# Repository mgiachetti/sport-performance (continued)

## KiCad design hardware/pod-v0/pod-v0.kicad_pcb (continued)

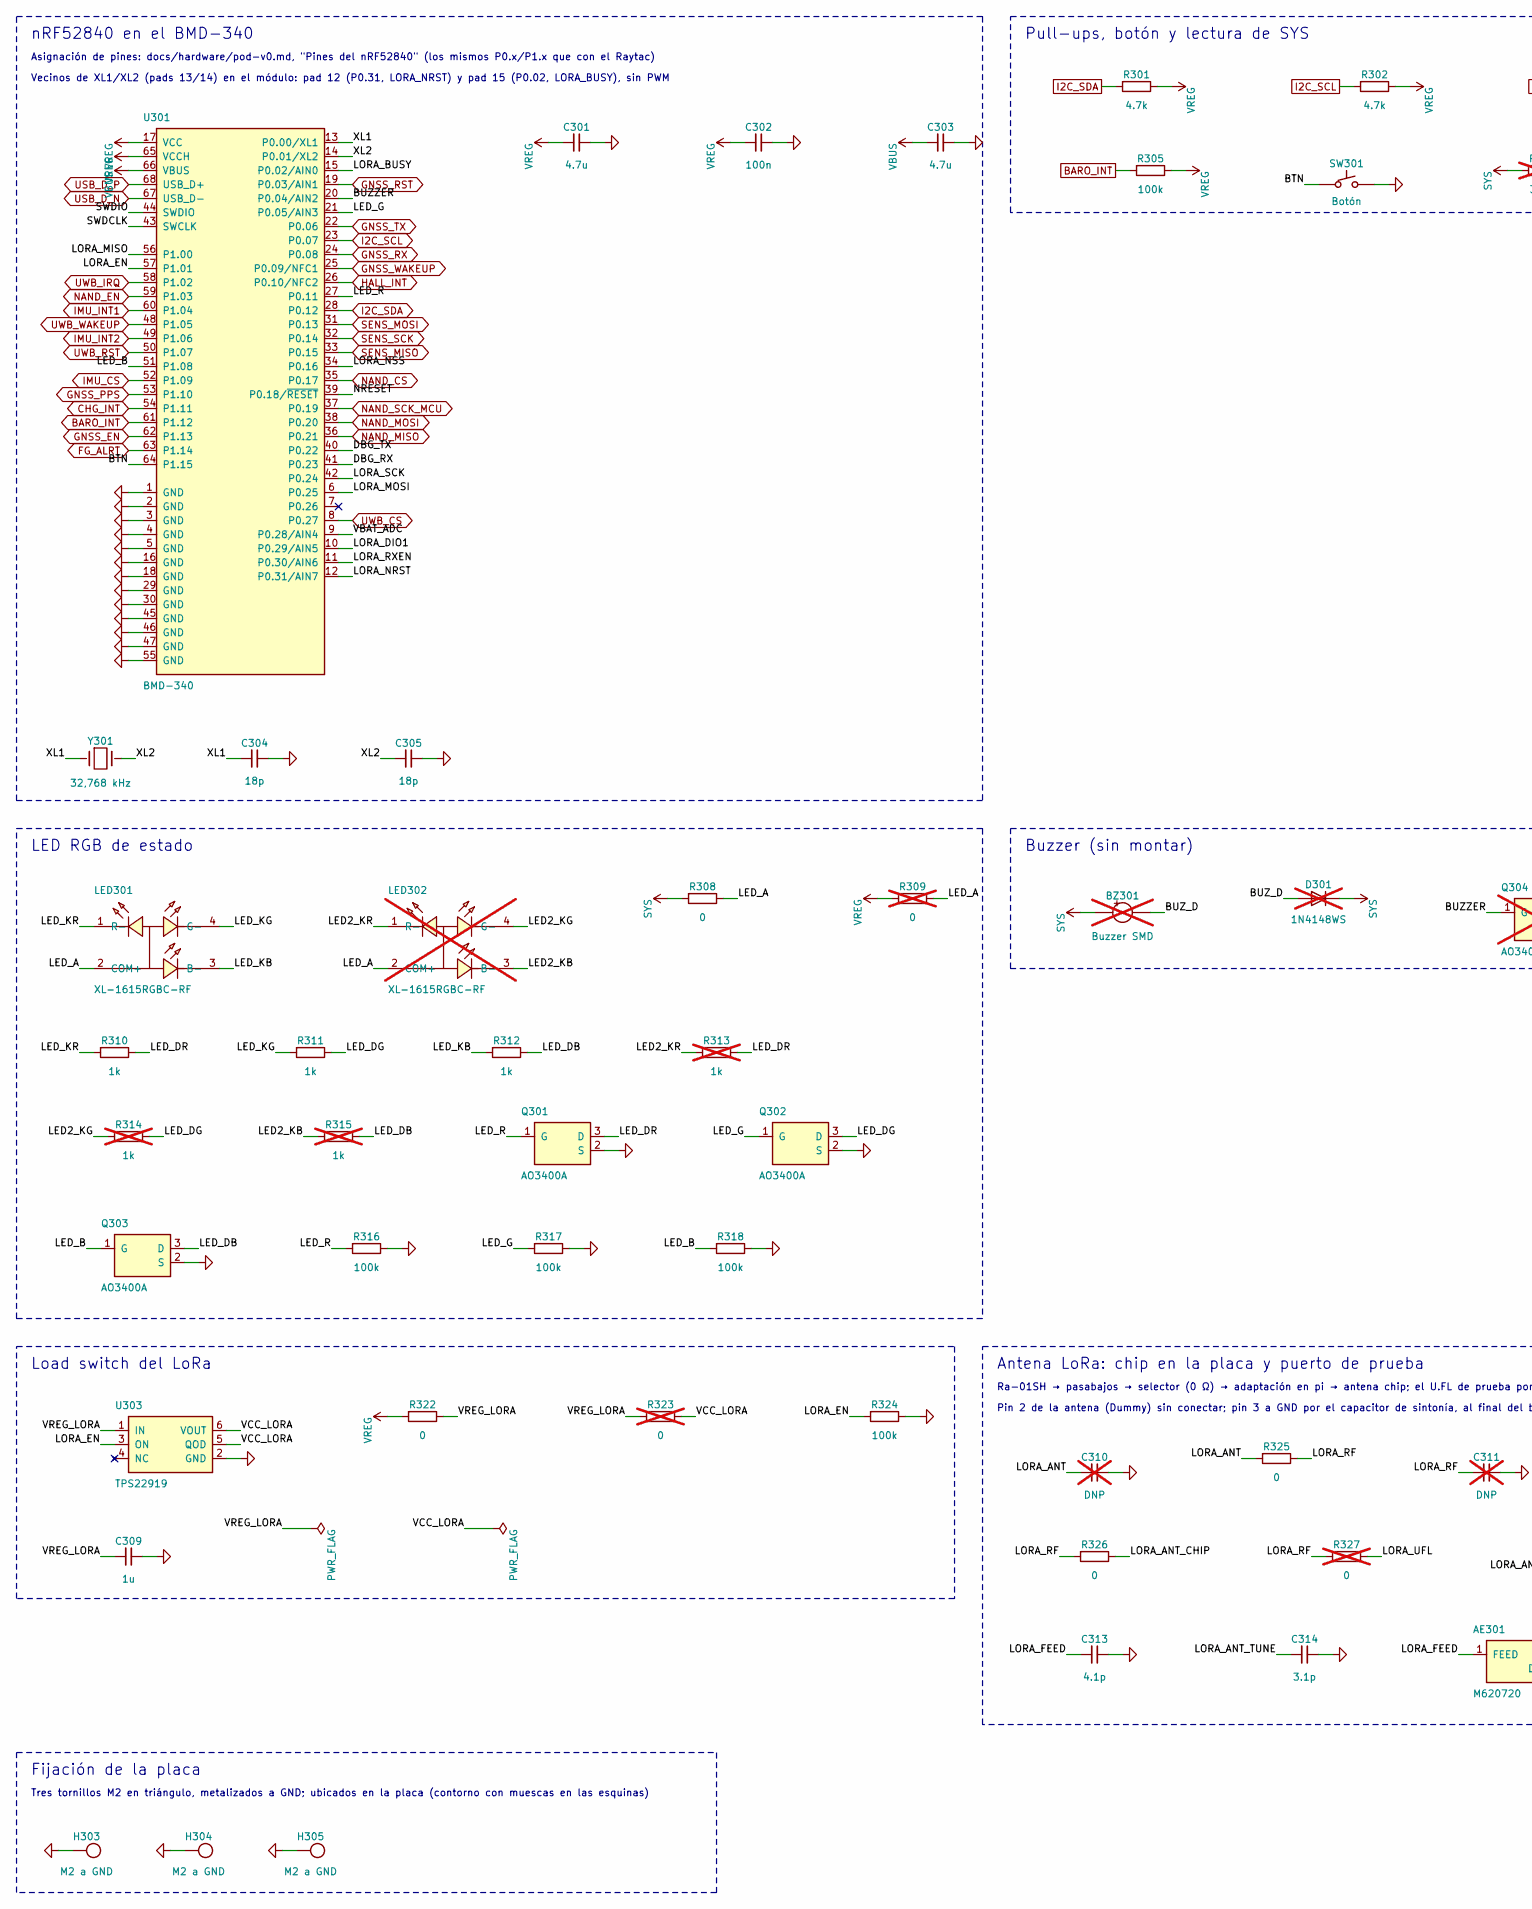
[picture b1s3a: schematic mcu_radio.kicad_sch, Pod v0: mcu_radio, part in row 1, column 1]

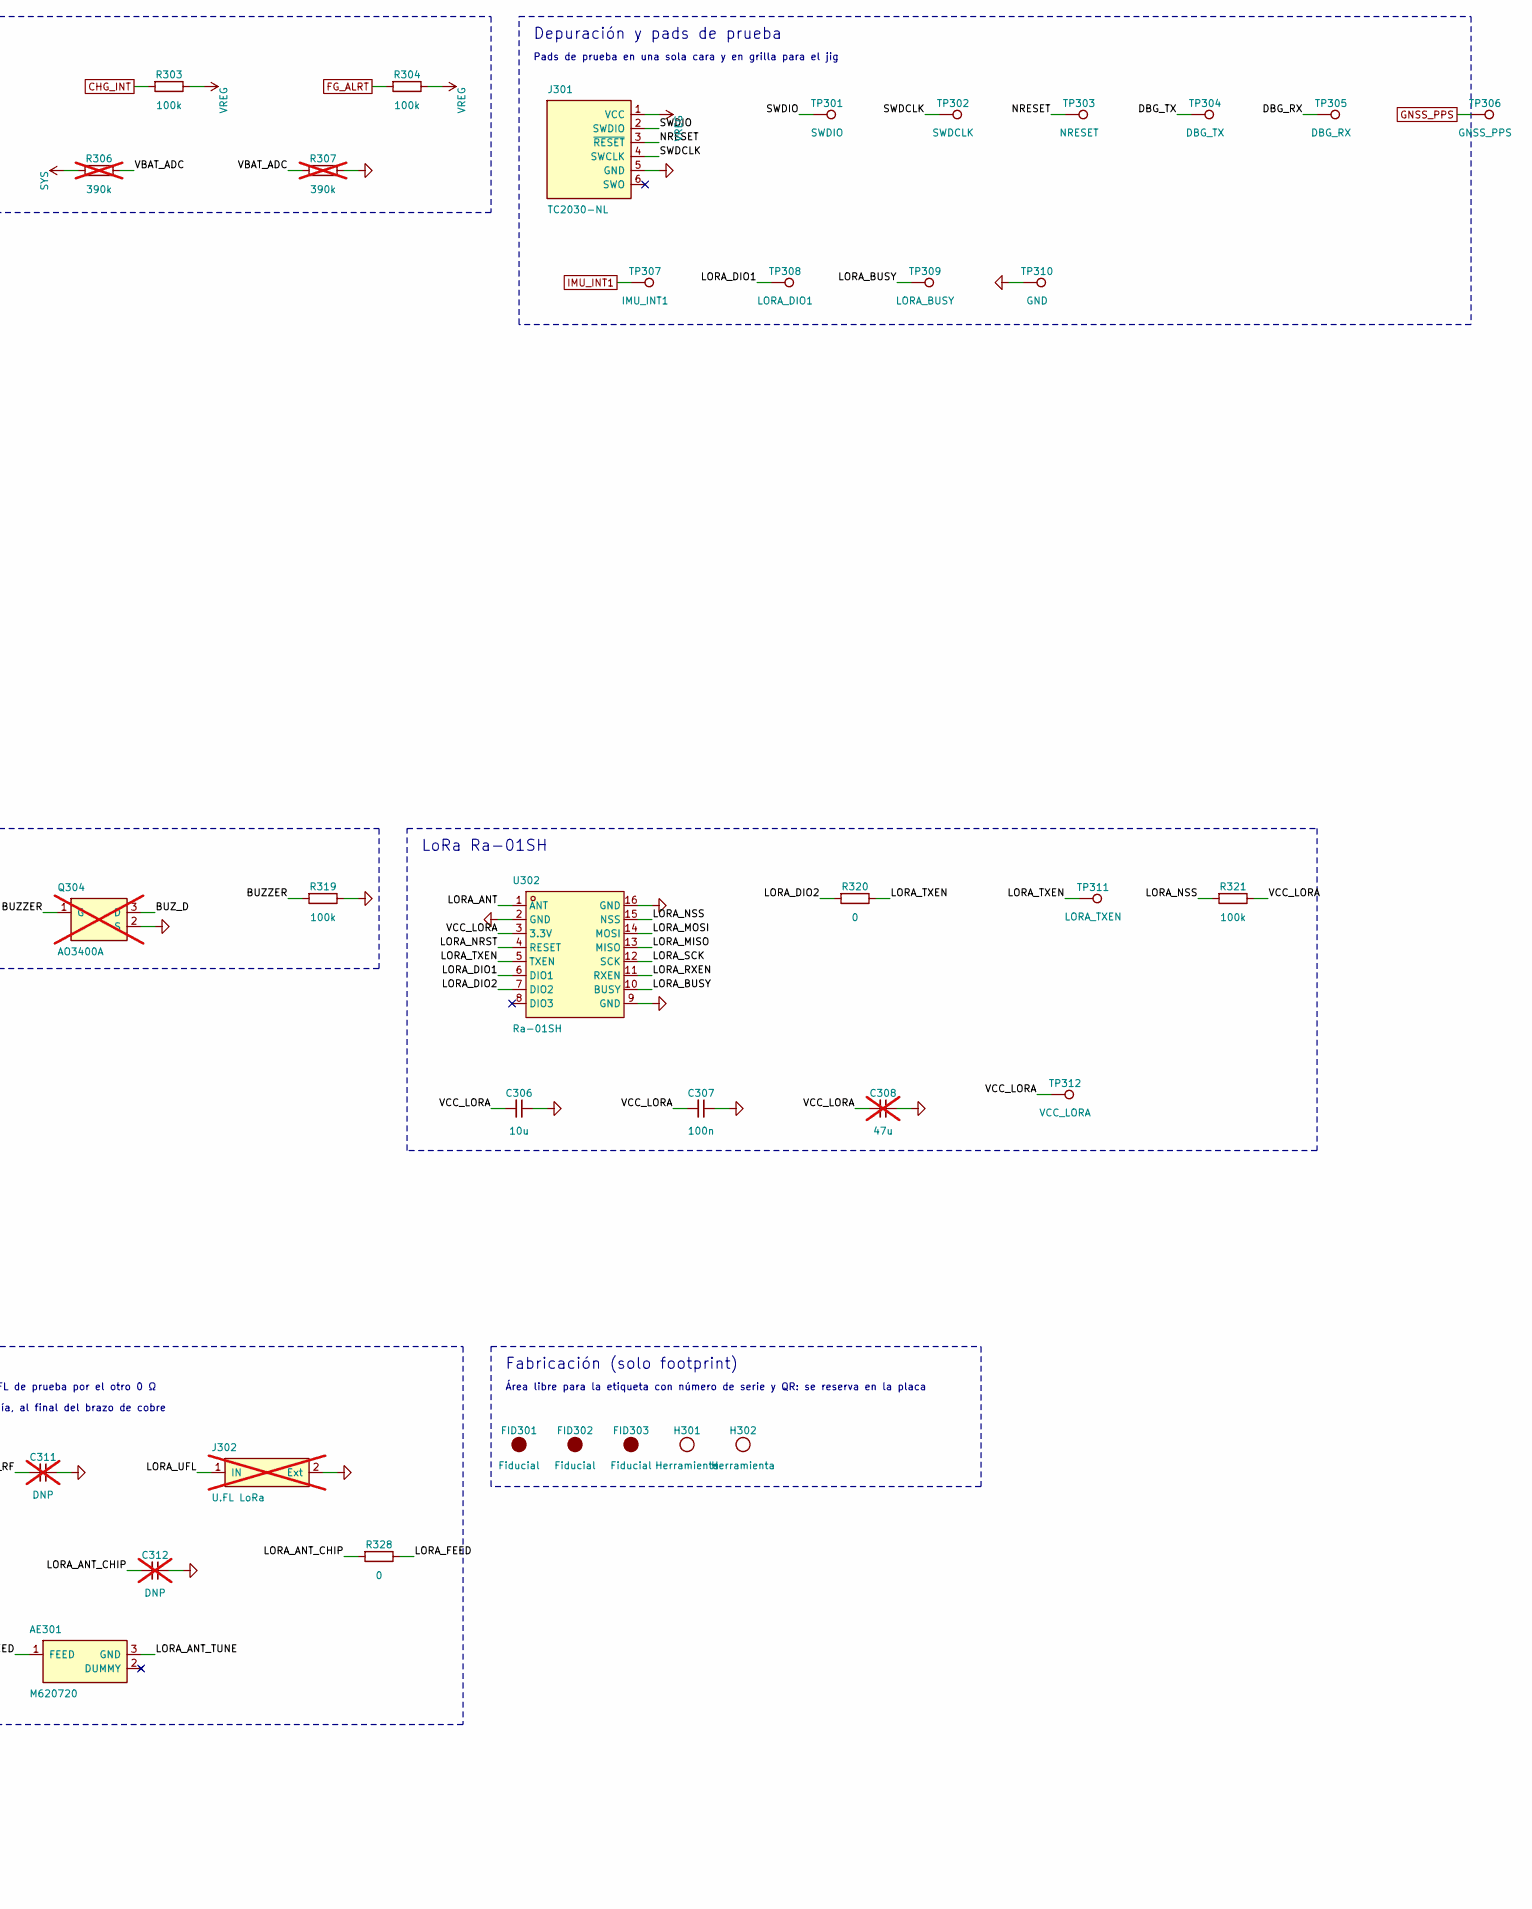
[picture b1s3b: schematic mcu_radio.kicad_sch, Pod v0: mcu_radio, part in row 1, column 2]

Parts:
AE301: M620720; KyoceraAVX_M620720_6.0x2.0mm; MPN M620720
BZ301: Buzzer SMD; MagneticBuzzer_CUI_CMT-8504-100-SMT; MPN CMT-8504-100-SMT-TR; LCSC C3811795; not fitted
C301, C303: 4.7u; C_0603_1608Metric; MPN CL10A475KO8NNNC; LCSC C19666
C302, C307: 100n; C_0402_1005Metric; MPN CL05B104KO5NNNC; LCSC C1525
C304, C305: 18p; C_0402_1005Metric; MPN CL05C180JB5NNNC; LCSC C307443
C306: 10u; C_0603_1608Metric; MPN CL10A106KP8NNNC; LCSC C19702
C308: 47u; C_1206_3216Metric; MPN CL31A476MQHNNNE; LCSC C68361; not fitted
C309: 1u; C_0402_1005Metric; MPN CL05A105KA5NQNC; LCSC C52923
C310, C311, C312: DNP; C_0402_1005Metric; not fitted
C313: 4.1p; C_0402_1005Metric; MPN GJM1555C1H4R1WB01D
C314: 3.1p; C_0402_1005Metric; MPN GJM1555C1H3R1WB01D
D301: 1N4148WS; D_SOD-323; MPN 1N4148WS; LCSC C2128; not fitted
FID301, FID302, FID303: Fiducial; Fiducial_1mm_Mask2mm
H301, H302: Herramienta; MountingHole_2.1mm
H303, H304, H305: M2 a GND; MountingHole_2.2mm_M2_Pad_Via
J301: TC2030-NL; Tag-Connect_TC2030-IDC-NL_2x03_P1.27mm_Vertical
J302: U.FL LoRa; U.FL_Hirose_U.FL-R-SMT-1_Vertical; MPN U.FL-R-SMT-1(10); LCSC C88373; not fitted
LED301: XL-1615RGBC-RF; LED-ARRAY-SMD_4P-L1.6-W1.5-BR_XL-1615RGBC-RF; MPN XL-1615RGBC-RF; LCSC C965840
LED302: XL-1615RGBC-RF; LED-ARRAY-SMD_4P-L1.6-W1.5-BR_XL-1615RGBC-RF; MPN XL-1615RGBC-RF; LCSC C965840; not fitted
Q301, Q302, Q303: AO3400A; SOT-23; MPN AO3400A; LCSC C20917
Q304: AO3400A; SOT-23; MPN AO3400A; LCSC C20917; not fitted
R301, R302: 4.7k; R_0402_1005Metric; MPN 0402WGF4701TCE; LCSC C25900
R303, R304, R305, R316, R317, R318, R319, R321, R324: 100k; R_0402_1005Metric; MPN 0402WGF1003TCE; LCSC C25741
R306, R307: 390k; R_0402_1005Metric; MPN 0402WGF3903TCE; LCSC C25782; not fitted
R308, R320, R322, R325, R326, R328: 0; R_0402_1005Metric; MPN 0402WGF0000TCE; LCSC C17168
R309, R323, R327: 0; R_0402_1005Metric; MPN 0402WGF0000TCE; LCSC C17168; not fitted
R310, R311, R312: 1k; R_0402_1005Metric; MPN 0402WGF1001TCE; LCSC C11702
R313, R314, R315: 1k; R_0402_1005Metric; MPN 0402WGF1001TCE; LCSC C11702; not fitted
SW301: Botón; SW_SPST_TL3342; MPN TL3342F450QG; LCSC C2886897
TP301: SWDIO; TestPoint_Pad_D1.0mm
TP302: SWDCLK; TestPoint_Pad_D1.0mm
TP303: NRESET; TestPoint_Pad_D1.0mm
TP304: DBG_TX; TestPoint_Pad_D1.0mm
TP305: DBG_RX; TestPoint_Pad_D1.0mm
TP306: GNSS_PPS; TestPoint_Pad_D1.0mm
TP307: IMU_INT1; TestPoint_Pad_D1.0mm
TP308: LORA_DIO1; TestPoint_Pad_D1.0mm
TP309: LORA_BUSY; TestPoint_Pad_D1.0mm
TP310: GND; TestPoint_Pad_D1.0mm
TP311: LORA_TXEN; TestPoint_Pad_D1.0mm
TP312: VCC_LORA; TestPoint_Pad_D1.0mm
U301: BMD-340; u-blox_BMD-340_15.0x10.2mm; MPN BMD-340-A-R
U302: Ra-01SH; WIRELM-SMD_RA-01SH; MPN Ra-01SH; LCSC C2764087
U303: TPS22919; SOT-363_SC-70-6; MPN TPS22919DCKR; LCSC C2149796
Y301: 32,768 kHz; Crystal_SMD_2012-2Pin_2.0x1.2mm; MPN CM8V-T1A-32.768KHZ-12.5PF-20PPM-TA-QC; LCSC C5341285

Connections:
/mcu_radio/BTN: SW301.1, U301.64 (P1.15)
/mcu_radio/BUZZER: Q304.1 (G), R319.1, U301.20 (P0.04/AIN2)
/mcu_radio/BUZ_D: BZ301.2 (-), D301.2 (A), Q304.3 (D)
/mcu_radio/DBG_RX: TP305.1, U301.41 (P0.23)
/mcu_radio/DBG_TX: TP304.1, U301.40 (P0.22)
/mcu_radio/LED2_KB: LED302.3 (B-), R315.1
/mcu_radio/LED2_KG: LED302.4 (G-), R314.1
/mcu_radio/LED2_KR: LED302.1 (R-), R313.1
/mcu_radio/LED_A: LED301.2 (COM+), LED302.2 (COM+), R308.2, R309.2
/mcu_radio/LED_B: Q303.1 (G), R318.1, U301.51 (P1.08)
/mcu_radio/LED_DB: Q303.3 (D), R312.2, R315.2
/mcu_radio/LED_DG: Q302.3 (D), R311.2, R314.2
/mcu_radio/LED_DR: Q301.3 (D), R310.2, R313.2
/mcu_radio/LED_G: Q302.1 (G), R317.1, U301.21 (P0.05/AIN3)
/mcu_radio/LED_KB: LED301.3 (B-), R312.1
/mcu_radio/LED_KG: LED301.4 (G-), R311.1
/mcu_radio/LED_KR: LED301.1 (R-), R310.1
/mcu_radio/LED_R: Q301.1 (G), R316.1, U301.27 (P0.11)
/mcu_radio/LORA_ANT: C310.1, R325.1, U302.1 (ANT)
/mcu_radio/LORA_ANT_CHIP: C312.1, R326.2, R328.1
/mcu_radio/LORA_ANT_TUNE: AE301.3 (GND), C314.1
/mcu_radio/LORA_BUSY: TP309.1, U301.15 (P0.02/AIN0), U302.10 (BUSY)
/mcu_radio/LORA_DIO1: TP308.1, U301.10 (P0.29/AIN5), U302.6 (DIO1)
/mcu_radio/LORA_DIO2: R320.1, U302.7 (DIO2)
/mcu_radio/LORA_EN: R324.1, U301.57 (P1.01), U303.3 (ON)
/mcu_radio/LORA_FEED: AE301.1 (FEED), C313.1, R328.2
/mcu_radio/LORA_MISO: U301.56 (P1.00), U302.13 (MISO)
/mcu_radio/LORA_MOSI: U301.6 (P0.25), U302.14 (MOSI)
/mcu_radio/LORA_NRST: U301.12 (P0.31/AIN7), U302.4 (RESET)
/mcu_radio/LORA_NSS: R321.1, U301.34 (P0.16), U302.15 (NSS)
/mcu_radio/LORA_RF: C311.1, R325.2, R326.1, R327.1
/mcu_radio/LORA_RXEN: U301.11 (P0.30/AIN6), U302.11 (RXEN)
/mcu_radio/LORA_SCK: U301.42 (P0.24), U302.12 (SCK)
/mcu_radio/LORA_TXEN: R320.2, TP311.1, U302.5 (TXEN)
/mcu_radio/LORA_UFL: J302.1 (IN), R327.2
/mcu_radio/NRESET: J301.3 (~RESET), TP303.1, U301.39 (P0.18/~RESET)
/mcu_radio/SWDCLK: J301.4 (SWCLK), TP302.1, U301.43 (SWCLK)
/mcu_radio/SWDIO: J301.2 (SWDIO), TP301.1, U301.44 (SWDIO)
/mcu_radio/VBAT_ADC: R306.2, R307.1, U301.9 (P0.28/AIN4)
/mcu_radio/VCC_LORA: C306.1, C307.1, C308.1, R321.2, R323.2, TP312.1, U302.3 (3.3V), U303.5 (QOD), U303.6 (VOUT)
/mcu_radio/VREG_LORA: C309.1, R322.2, R323.1, U303.1 (IN)
/mcu_radio/XL1: C304.1, U301.13 (P0.00/XL1), Y301.1
/mcu_radio/XL2: C305.1, U301.14 (P0.01/XL2), Y301.2
BARO_INT: R305.1, U301.61 (P1.12); also elsewhere on the board
CHG_INT: R303.1, U301.54 (P1.11); also elsewhere on the board
FG_ALRT: R304.1, U301.63 (P1.14); also elsewhere on the board
GND: C301.2, C302.2, C303.2, C304.2, C305.2, C306.2, C307.2, C308.2, C309.2, C310.2, C311.2, C312.2, C313.2, C314.2, H303.1, H304.1, H305.1, J301.5 (GND), J302.2 (Ext), Q301.2 (S), Q302.2 (S), Q303.2 (S), Q304.2 (S), R307.2, R316.2, R317.2, R318.2, R319.2, R324.2, SW301.2, TP310.1, U301.1 (GND), U301.2 (GND), U301.3 (GND), U301.4 (GND), U301.5 (GND), U301.16 (GND), U301.18 (GND), U301.29 (GND), U301.30 (GND), U301.45 (GND), U301.46 (GND), U301.47 (GND), U301.55 (GND), U302.2 (GND), U302.9 (GND), U302.16 (GND), U303.2 (GND); also elsewhere on the board
GNSS_EN: U301.62 (P1.13); also elsewhere on the board
GNSS_PPS: TP306.1, U301.53 (P1.10); also elsewhere on the board
GNSS_RST: U301.19 (P0.03/AIN1); also elsewhere on the board
GNSS_RX: U301.24 (P0.08); also elsewhere on the board
GNSS_TX: U301.22 (P0.06); also elsewhere on the board
GNSS_WAKEUP: U301.25 (P0.09/NFC1); also elsewhere on the board
HALL_INT: U301.26 (P0.10/NFC2); also elsewhere on the board
I2C_SCL: R302.1, U301.23 (P0.07); also elsewhere on the board
I2C_SDA: R301.1, U301.28 (P0.12); also elsewhere on the board
IMU_CS: U301.52 (P1.09); also elsewhere on the board
IMU_INT1: TP307.1, U301.60 (P1.04); also elsewhere on the board
IMU_INT2: U301.49 (P1.06); also elsewhere on the board
NAND_CS: U301.35 (P0.17); also elsewhere on the board
NAND_EN: U301.59 (P1.03); also elsewhere on the board
NAND_MISO: U301.36 (P0.21); also elsewhere on the board
NAND_MOSI: U301.38 (P0.20); also elsewhere on the board
NAND_SCK_MCU: U301.37 (P0.19); also elsewhere on the board
SENS_MISO: U301.33 (P0.15); also elsewhere on the board
SENS_MOSI: U301.31 (P0.13); also elsewhere on the board
SENS_SCK: U301.32 (P0.14); also elsewhere on the board
SYS: BZ301.1 (+), D301.1 (K), R306.1, R308.1; also elsewhere on the board
USB_D_N: U301.67 (USB_D-); also elsewhere on the board
USB_D_P: U301.68 (USB_D+); also elsewhere on the board
UWB_CS: U301.8 (P0.27); also elsewhere on the board
UWB_IRQ: U301.58 (P1.02); also elsewhere on the board
UWB_RST: U301.50 (P1.07); also elsewhere on the board
UWB_WAKEUP: U301.48 (P1.05); also elsewhere on the board
VBUS: C303.1, U301.66 (VBUS); also elsewhere on the board
VREG: C301.1, C302.1, J301.1 (VCC), R301.2, R302.2, R303.2, R304.2, R305.2, R309.1, R322.1, U301.17 (VCC), U301.65 (VCCH); also elsewhere on the board

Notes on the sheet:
nRF52840 en el BMD-340
Asignación de pines: docs/hardware/pod-v0.md, "Pines del nRF52840" (los mismos P0.x/P1.x que con el Raytac)
Vecinos de XL1/XL2 (pads 13/14) en el módulo: pad 12 (P0.31, LORA_NRST) y pad 15 (P0.02, LORA_BUSY), sin PWM
Pull-ups, botón y lectura de SYS
Depuración y pads de prueba
Pads de prueba en una sola cara y en grilla para el jig
LED RGB de estado
Buzzer (sin montar)
LoRa Ra-01SH
Load switch del LoRa
Antena LoRa: chip en la placa y puerto de prueba
Ra-01SH → pasabajos → selector (0 Ω) → adaptación en pi → antena chip; el U.FL de prueba por el otro 0 Ω
Pin 2 de la antena (Dummy) sin conectar; pin 3 a GND por el capacitor de sintonía, al final del brazo de cobre
Fabricación (solo footprint)
Área libre para la etiqueta con número de serie y QR: se reserva en la placa
Fijación de la placa
Tres tornillos M2 en triángulo, metalizados a GND; ubicados en la placa (contorno con muescas en las esquinas)

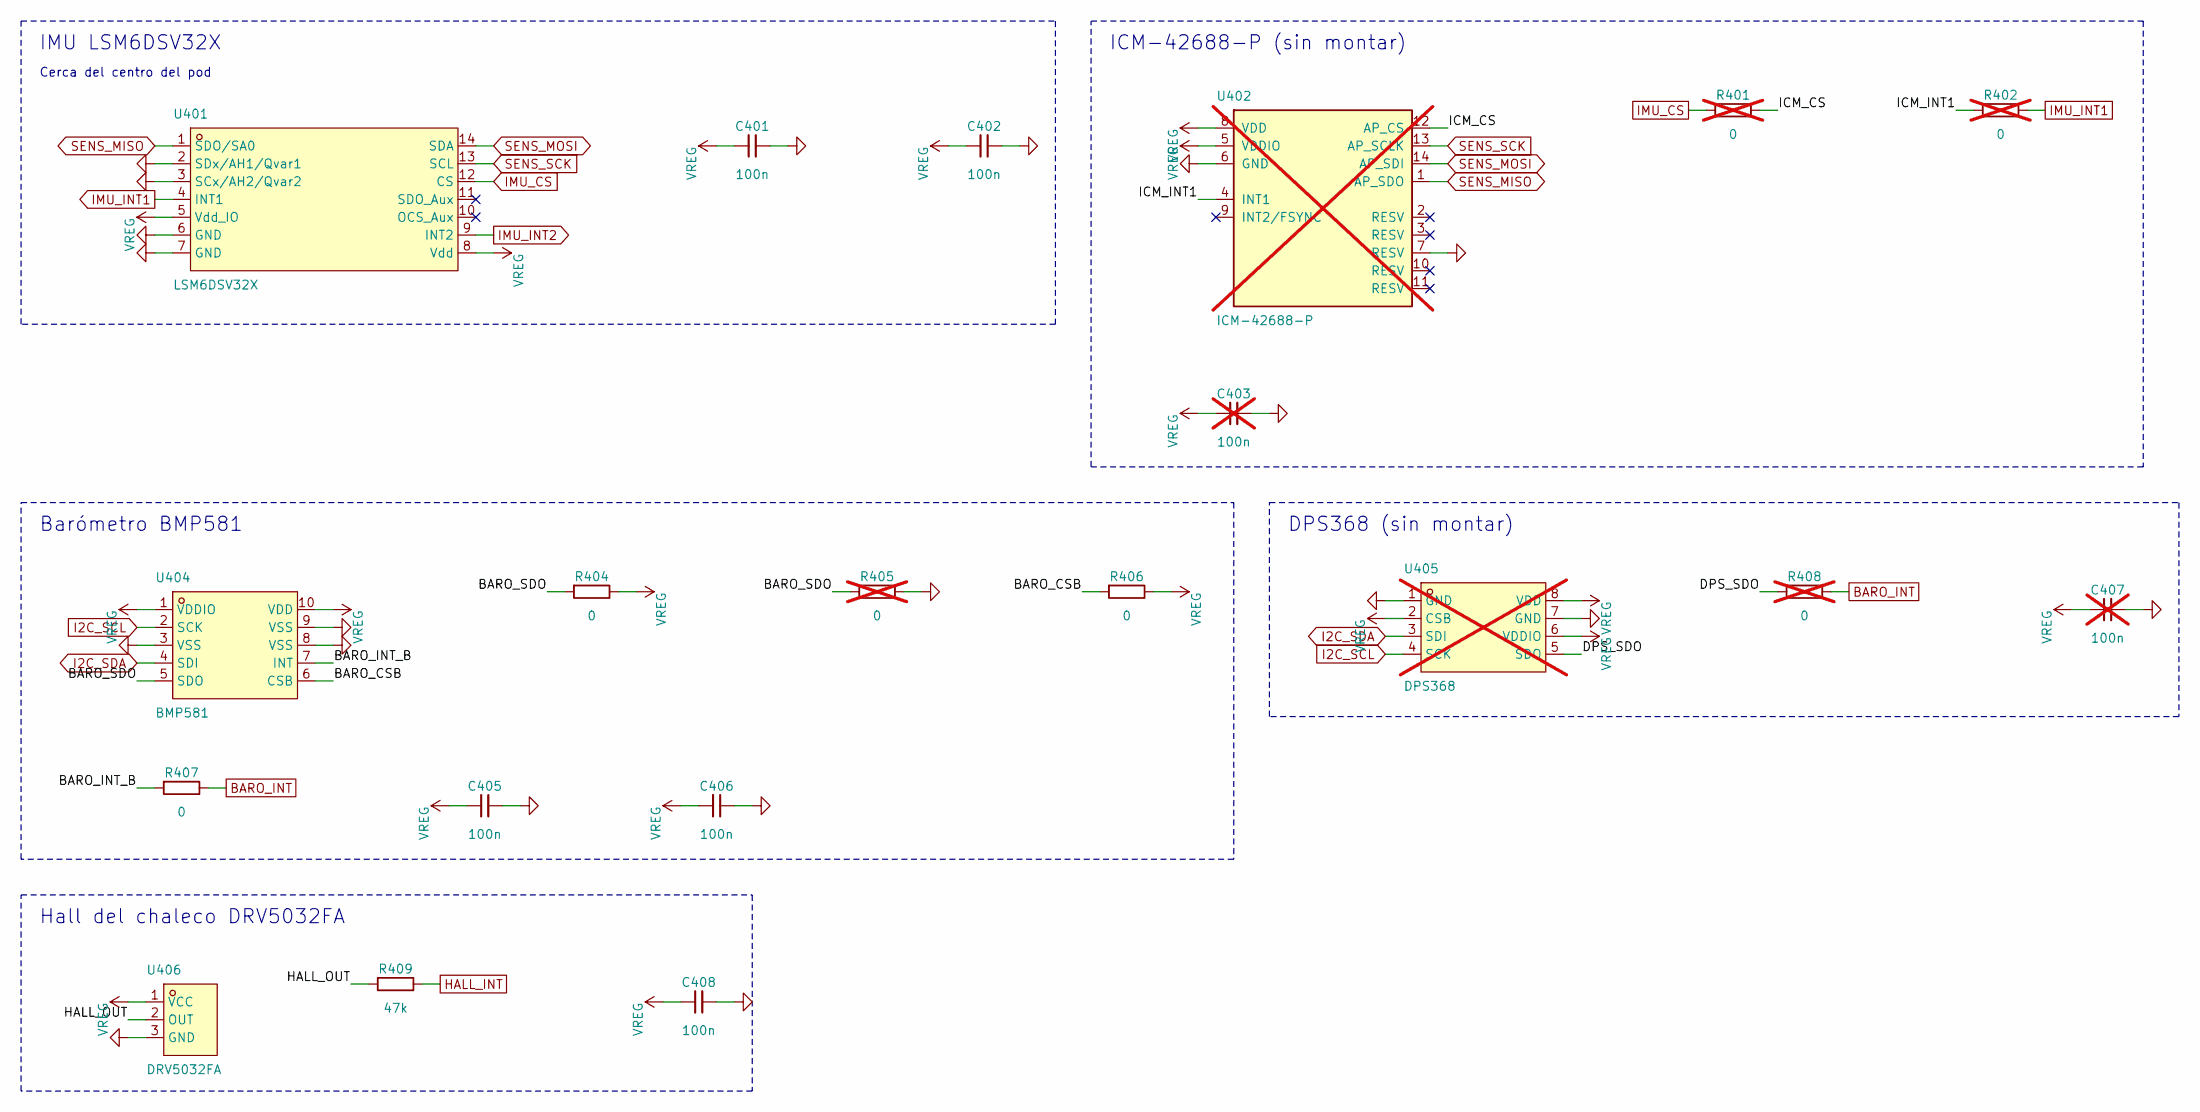
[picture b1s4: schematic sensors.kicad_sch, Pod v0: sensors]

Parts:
C401, C402, C405, C406, C408: 100n; C_0402_1005Metric; MPN CL05B104KO5NNNC; LCSC C1525
C403, C407: 100n; C_0402_1005Metric; MPN CL05B104KO5NNNC; LCSC C1525; not fitted
R401, R402, R405, R408: 0; R_0402_1005Metric; MPN 0402WGF0000TCE; LCSC C17168; not fitted
R404, R406, R407: 0; R_0402_1005Metric; MPN 0402WGF0000TCE; LCSC C17168
R409: 47k; R_0402_1005Metric; MPN 0402WGF4702TCE; LCSC C25792
U401: LSM6DSV32X; LGA-14_L3.0-W2.5-P0.50-TL; MPN LSM6DSV32XTR; LCSC C22461202
U402: ICM-42688-P; LGA-14_3x2.5mm_P0.5mm_LayoutBorder3x4y; MPN ICM-42688-P; LCSC C1850418; not fitted
U404: BMP581; LGA-10_L2.0-W2.0-P0.50-TL_BMP581; MPN BMP581; LCSC C5362283
U405: DPS368; LGA-8_L2.5-W2.0-P0.65-TR_DPS368; MPN DPS368XTSA1; LCSC C3232508; not fitted
U406: DRV5032FA; SOT-23_L2.9-W1.3-P1.90-LS2.4-BR; MPN DRV5032FADBZR; LCSC C140921

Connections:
/sensors/BARO_CSB: R406.1, U404.6 (CSB)
/sensors/BARO_INT_B: R407.1, U404.7 (INT)
/sensors/BARO_SDO: R404.1, R405.1, U404.5 (SDO)
/sensors/DPS_SDO: R408.1, U405.5 (SDO)
/sensors/HALL_OUT: R409.1, U406.2 (OUT)
/sensors/ICM_CS: R401.2, U402.12 (AP_CS)
/sensors/ICM_INT1: R402.1, U402.4 (INT1)
BARO_INT: R407.2, R408.2; also elsewhere on the board
GND: C401.2, C402.2, C403.2, C405.2, C406.2, C407.2, C408.2, R405.2, U401.2 (SDx/AH1/Qvar1), U401.3 (SCx/AH2/Qvar2), U401.6 (GND), U401.7 (GND), U402.6 (GND), U402.7 (RESV), U404.3 (VSS), U404.8 (VSS), U404.9 (VSS), U405.1 (GND), U405.7 (GND), U406.3 (GND); also elsewhere on the board
HALL_INT: R409.2; also elsewhere on the board
I2C_SCL: U404.2 (SCK), U405.4 (SCK); also elsewhere on the board
I2C_SDA: U404.4 (SDI), U405.3 (SDI); also elsewhere on the board
IMU_CS: R401.1, U401.12 (CS); also elsewhere on the board
IMU_INT1: R402.2, U401.4 (INT1); also elsewhere on the board
IMU_INT2: U401.9 (INT2); also elsewhere on the board
SENS_MISO: U401.1 (SDO/SA0), U402.1 (AP_SDO); also elsewhere on the board
SENS_MOSI: U401.14 (SDA), U402.14 (AP_SDI); also elsewhere on the board
SENS_SCK: U401.13 (SCL), U402.13 (AP_SCLK); also elsewhere on the board
VREG: C401.1, C402.1, C403.1, C405.1, C406.1, C407.1, C408.1, R404.2, R406.2, U401.5 (Vdd_IO), U401.8 (Vdd), U402.5 (VDDIO), U402.8 (VDD), U404.1 (VDDIO), U404.10 (VDD), U405.2 (CSB), U405.6 (VDDIO), U405.8 (VDD), U406.1 (VCC); also elsewhere on the board

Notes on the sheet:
IMU LSM6DSV32X
Cerca del centro del pod
ICM-42688-P (sin montar)
Barómetro BMP581
DPS368 (sin montar)
Hall del chaleco DRV5032FA

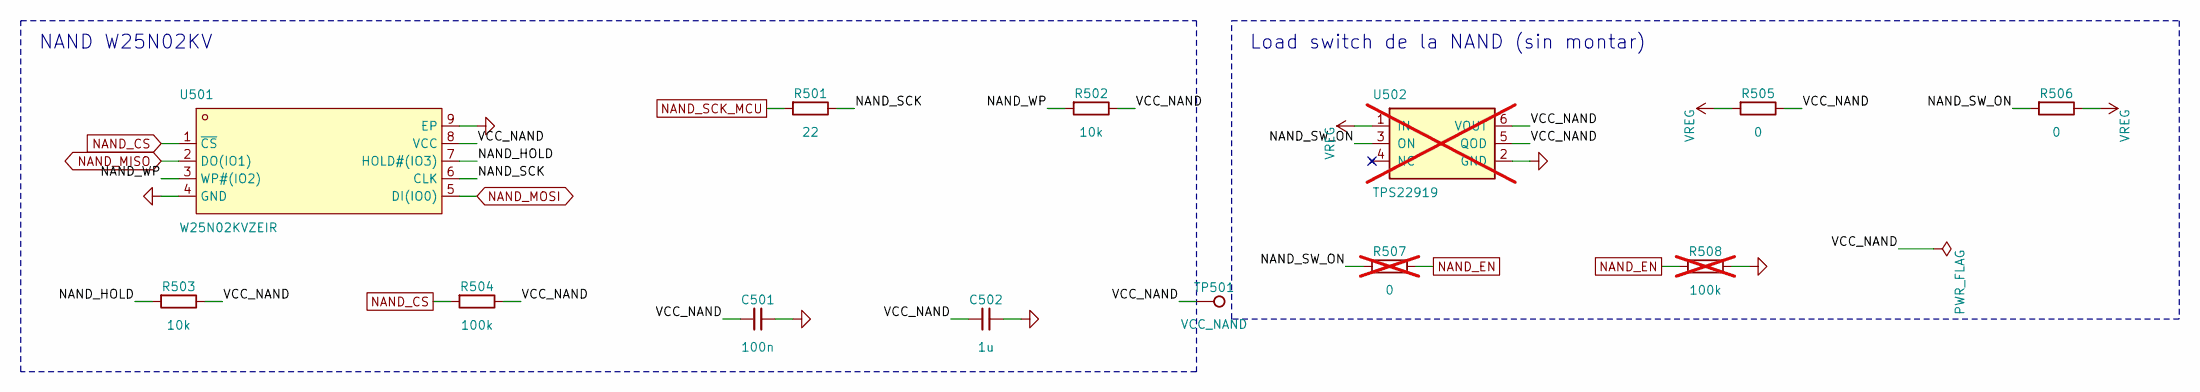
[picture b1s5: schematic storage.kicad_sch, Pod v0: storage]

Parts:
C501: 100n; C_0402_1005Metric; MPN CL05B104KO5NNNC; LCSC C1525
C502: 1u; C_0402_1005Metric; MPN CL05A105KA5NQNC; LCSC C52923
R501: 22; R_0402_1005Metric; MPN 0402WGF220JTCE; LCSC C25092
R502, R503: 10k; R_0402_1005Metric; MPN 0402WGF1002TCE; LCSC C25744
R504: 100k; R_0402_1005Metric; MPN 0402WGF1003TCE; LCSC C25741
R505, R506: 0; R_0402_1005Metric; MPN 0402WGF0000TCE; LCSC C17168
R507: 0; R_0402_1005Metric; MPN 0402WGF0000TCE; LCSC C17168; not fitted
R508: 100k; R_0402_1005Metric; MPN 0402WGF1003TCE; LCSC C25741; not fitted
TP501: VCC_NAND; TestPoint_Pad_D1.0mm
U501: W25N02KVZEIR; WSON-8_L8.0-W6.0-P1.27-TL-EP-1; MPN W25N02KVZEIR; LCSC C3010298
U502: TPS22919; SOT-363_SC-70-6; MPN TPS22919DCKR; LCSC C2149796; not fitted

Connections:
/storage/NAND_HOLD: R503.1, U501.7 (HOLD#(IO3))
/storage/NAND_SCK: R501.2, U501.6 (CLK)
/storage/NAND_SW_ON: R506.1, R507.1, U502.3 (ON)
/storage/NAND_WP: R502.1, U501.3 (WP#(IO2))
/storage/VCC_NAND: C501.1, C502.1, R502.2, R503.2, R504.2, R505.2, TP501.1, U501.8 (VCC), U502.5 (QOD), U502.6 (VOUT)
GND: C501.2, C502.2, R508.2, U501.4 (GND), U501.9 (EP), U502.2 (GND); also elsewhere on the board
NAND_CS: R504.1, U501.1 (~CS); also elsewhere on the board
NAND_EN: R507.2, R508.1; also elsewhere on the board
NAND_MISO: U501.2 (DO(IO1)); also elsewhere on the board
NAND_MOSI: U501.5 (DI(IO0)); also elsewhere on the board
NAND_SCK_MCU: R501.1; also elsewhere on the board
VREG: R505.1, R506.2, U502.1 (IN); also elsewhere on the board

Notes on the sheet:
NAND W25N02KV
Load switch de la NAND (sin montar)

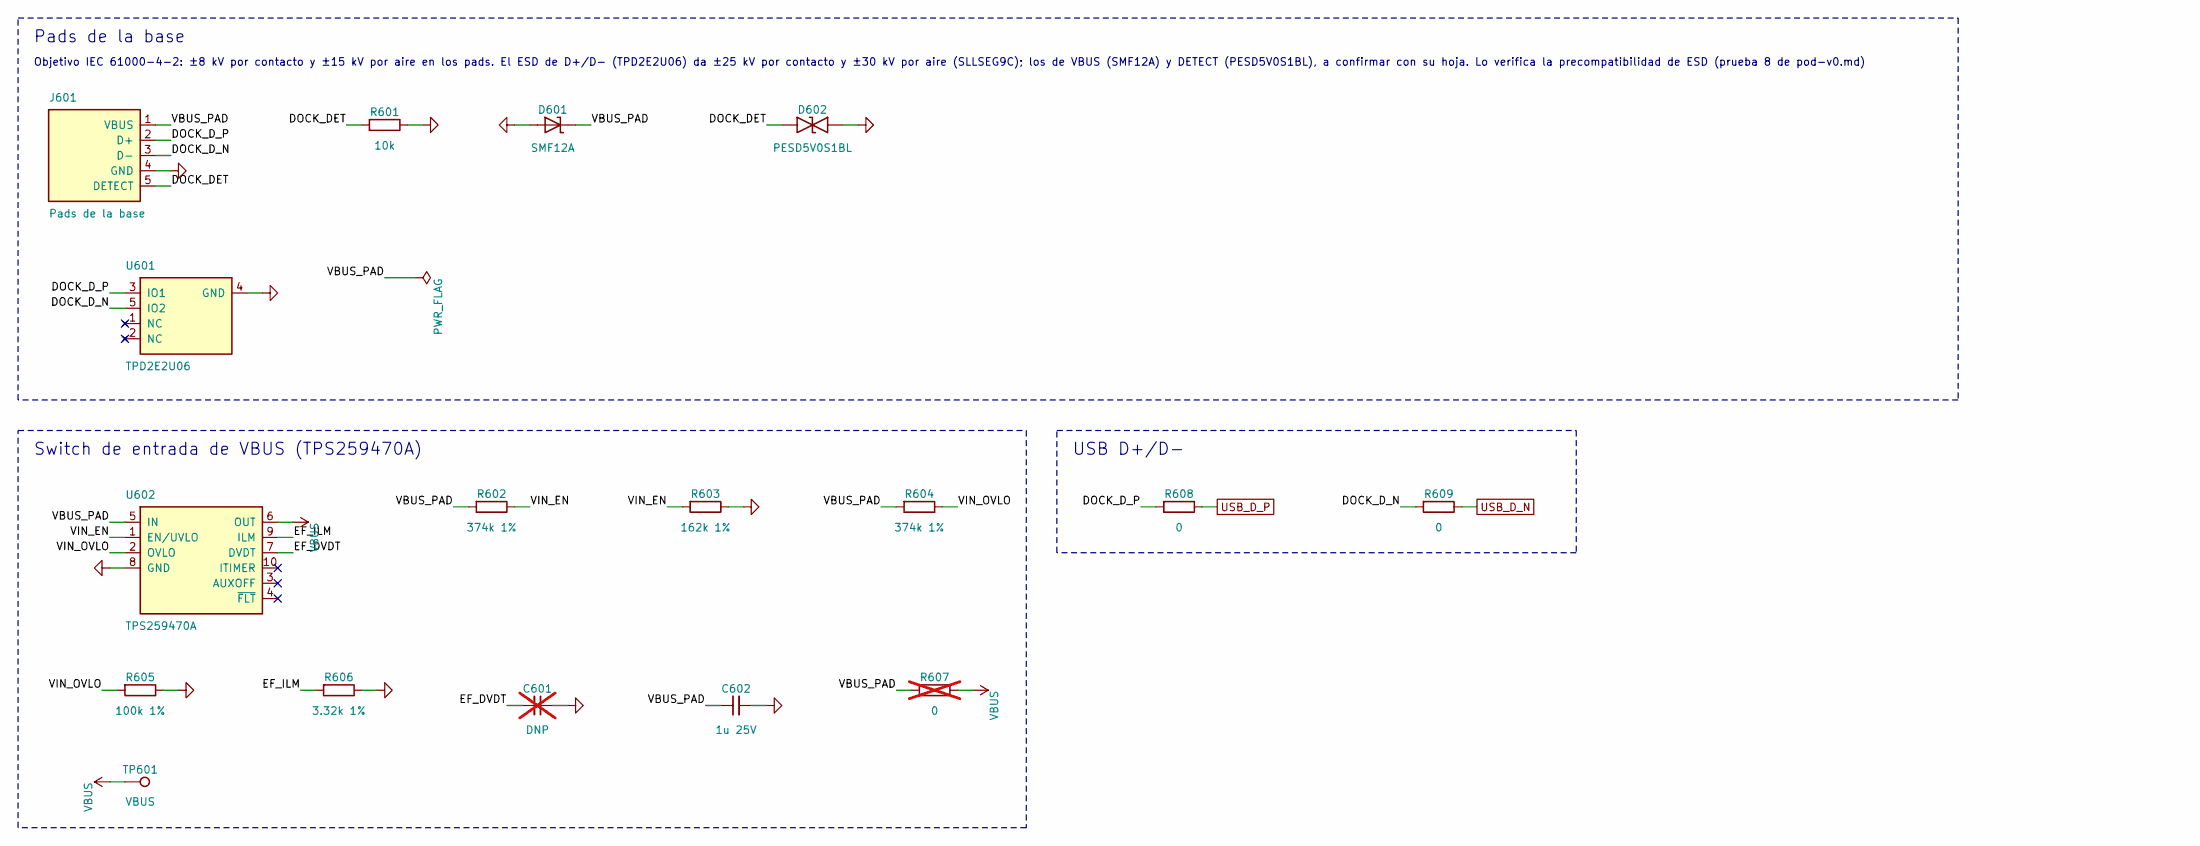
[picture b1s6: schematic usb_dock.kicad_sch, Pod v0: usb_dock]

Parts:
C601: DNP; C_0402_1005Metric; not fitted
C602: 1u 25V; C_0603_1608Metric; MPN CL10A105KA8NNNC; LCSC C5673
D601: SMF12A; D_SOD-123F; MPN SMF12A; LCSC C207255
D602: PESD5V0S1BL; D_SOD-882; MPN PESD5V0S1BL,315; LCSC C84374
J601: Pads de la base; Pod_Insert_Springs_5P_D2.0mm_P3.5mm
R601: 10k; R_0402_1005Metric; MPN 0402WGF1002TCE; LCSC C25744
R602, R604: 374k 1%; R_0402_1005Metric; MPN 0402WGF3743TCE; LCSC C25781
R603: 162k 1%; R_0402_1005Metric; MPN 0402WGF1623TCE; LCSC C54068
R605: 100k 1%; R_0402_1005Metric; MPN 0402WGF1003TCE; LCSC C25741
R606: 3.32k 1%; R_0402_1005Metric; MPN 0402WGF3321TCE; LCSC C60075
R607: 0; R_0402_1005Metric; MPN 0402WGF0000TCE; LCSC C17168; not fitted
R608, R609: 0; R_0402_1005Metric; MPN 0402WGF0000TCE; LCSC C17168
TP601: VBUS; TestPoint_Pad_D1.0mm
U601: TPD2E2U06; Texas_R-PDSO-N5_DRL-5; MPN TPD2E2U06DRLR; LCSC C1972959
U602: TPS259470A; Texas_RPW0010A_VQFN-HR-10_2x2mm_P0.45mm; MPN TPS259470ARPWR; LCSC C3662799

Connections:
/usb_dock/DOCK_DET: D602.1, J601.5 (DETECT), R601.1
/usb_dock/DOCK_D_N: J601.3 (D-), R609.1, U601.5 (IO2)
/usb_dock/DOCK_D_P: J601.2 (D+), R608.1, U601.3 (IO1)
/usb_dock/EF_DVDT: C601.1, U602.7 (DVDT)
/usb_dock/EF_ILM: R606.1, U602.9 (ILM)
/usb_dock/VBUS_PAD: C602.1, D601.1 (K), J601.1 (VBUS), R602.1, R604.1, R607.1, U602.5 (IN)
/usb_dock/VIN_EN: R602.2, R603.1, U602.1 (EN/UVLO)
/usb_dock/VIN_OVLO: R604.2, R605.1, U602.2 (OVLO)
GND: C601.2, C602.2, D601.2 (A), D602.2, J601.4 (GND), R601.2, R603.2, R605.2, R606.2, U601.4 (GND), U602.8 (GND); also elsewhere on the board
USB_D_N: R609.2; also elsewhere on the board
USB_D_P: R608.2; also elsewhere on the board
VBUS: R607.2, TP601.1, U602.6 (OUT); also elsewhere on the board

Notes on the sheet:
Pads de la base
Objetivo IEC 61000-4-2: ±8 kV por contacto y ±15 kV por aire en los pads. El ESD de D+/D− (TPD2E2U06) da ±25 kV por contacto y ±30 kV por aire (SLLSEG9C); los de VBUS (SMF12A) y DETECT (PESD5V0S1BL), a confirmar con su hoja. Lo verifica la precompatibilidad de ESD (prueba 8 de pod-v0.md)
Switch de entrada de VBUS (TPS259470A)
USB D+/D−

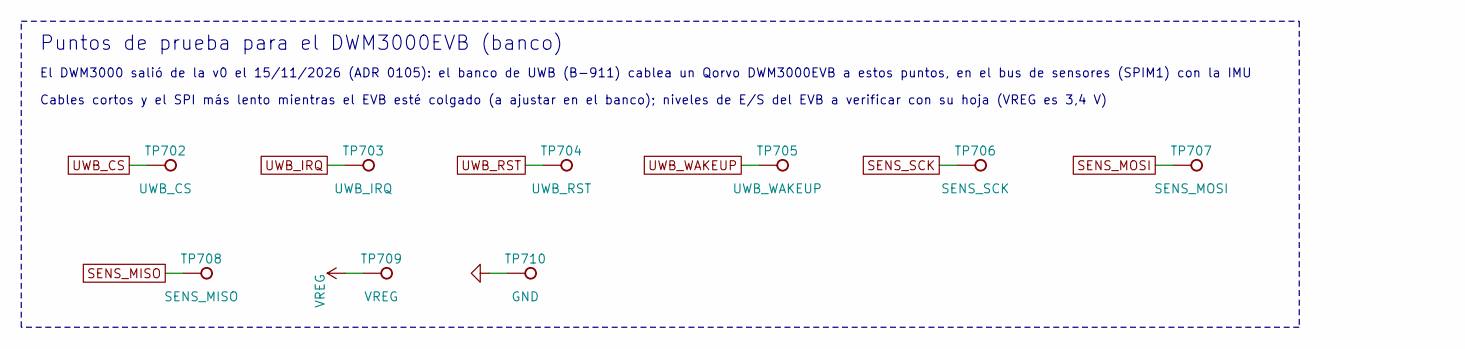
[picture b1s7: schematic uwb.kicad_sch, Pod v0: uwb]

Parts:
TP702: UWB_CS; TestPoint_Pad_D1.0mm
TP703: UWB_IRQ; TestPoint_Pad_D1.0mm
TP704: UWB_RST; TestPoint_Pad_D1.0mm
TP705: UWB_WAKEUP; TestPoint_Pad_D1.0mm
TP706: SENS_SCK; TestPoint_Pad_D1.0mm
TP707: SENS_MOSI; TestPoint_Pad_D1.0mm
TP708: SENS_MISO; TestPoint_Pad_D1.0mm
TP709: VREG; TestPoint_Pad_D1.0mm
TP710: GND; TestPoint_Pad_D1.0mm

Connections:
GND: TP710.1; also elsewhere on the board
SENS_MISO: TP708.1; also elsewhere on the board
SENS_MOSI: TP707.1; also elsewhere on the board
SENS_SCK: TP706.1; also elsewhere on the board
UWB_CS: TP702.1; also elsewhere on the board
UWB_IRQ: TP703.1; also elsewhere on the board
UWB_RST: TP704.1; also elsewhere on the board
UWB_WAKEUP: TP705.1; also elsewhere on the board
VREG: TP709.1; also elsewhere on the board

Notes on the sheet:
Puntos de prueba para el DWM3000EVB (banco)
El DWM3000 salió de la v0 el 15/11/2026 (ADR 0105): el banco de UWB (B-911) cablea un Qorvo DWM3000EVB a estos puntos, en el bus de sensores (SPIM1) con la IMU
Cables cortos y el SPI más lento mientras el EVB esté colgado (a ajustar en el banco); niveles de E/S del EVB a verificar con su hoja (VREG es 3,4 V)
